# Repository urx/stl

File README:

STL - Sequential Tail Lights
============================

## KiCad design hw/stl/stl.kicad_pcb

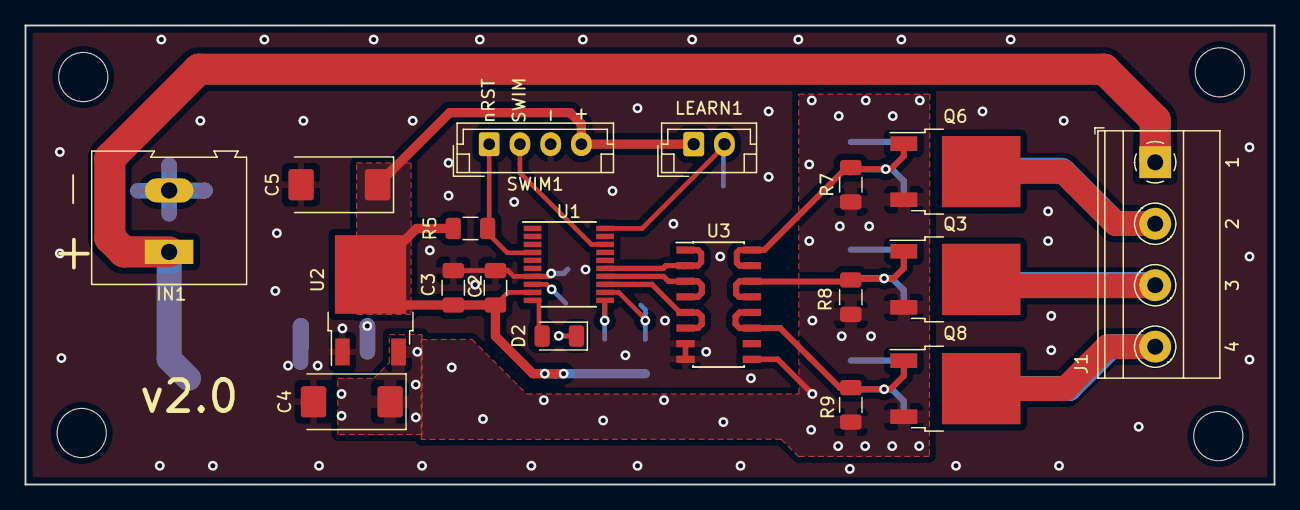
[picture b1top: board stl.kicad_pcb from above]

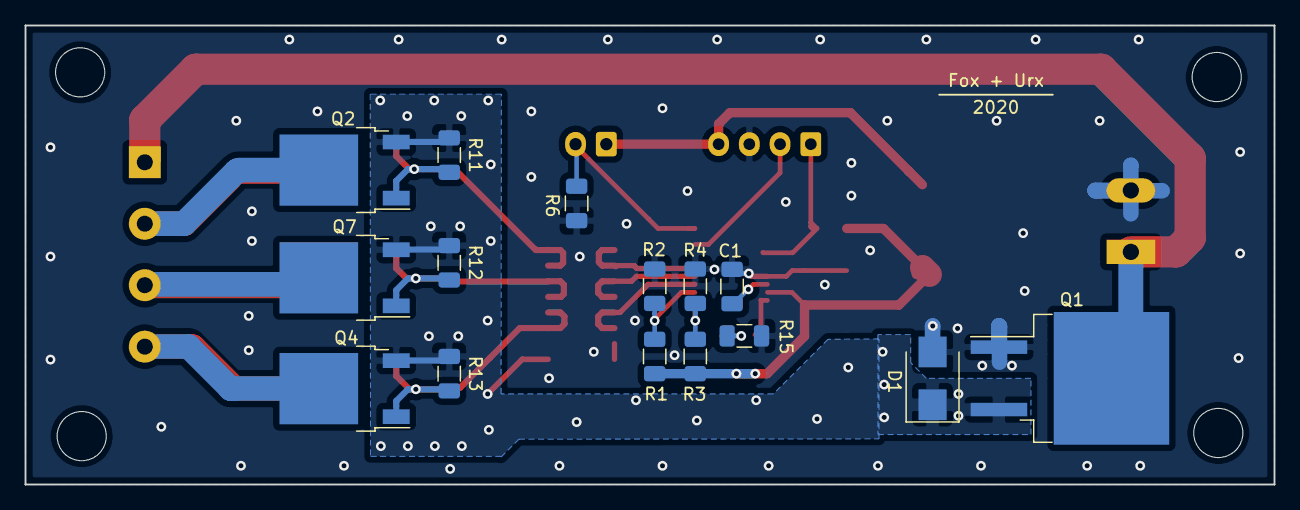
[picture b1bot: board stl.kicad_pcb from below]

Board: 2 copper layers, 101.6 x 37.3 mm, 34 parts (15 on the bottom side), 21 nets.

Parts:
C1, C3: 1uF; C_1206_3216Metric
C2: 0.1uF; C_1206_3216Metric
C4: 1uF; CP_EIA-7343-15_Kemet-W
C5: 10uF; CP_EIA-7343-15_Kemet-W
D1: SMBJ15A; D_SMB
D2: LED; LED_1206_3216Metric
IN1: Screw_Terminal_01x02; TerminalBlock_Altech_AK300-2_P5.00mm
J1: Screw_Terminal_01x04; TerminalBlock_Phoenix_MKDS-1,5-4_1x04_P5.00mm_Horizontal
LEARN1: Conn_01x02_Male; JST_EH_B02B-EH-A_1x02_P2.50mm_Vertical
Q1: IRF4905; TO-263-2
Q2: IRFR5505TRLPBF; TO-252-2
Q3, Q4, Q6, Q7, Q8: 5505; TO-252-2
R1, R2, R3, R4, R5, R6, R7, R8, R9, R11, R12, R13: 1K; R_1206_3216Metric
R15: 68; R_1206_3216Metric
SWIM1: Conn_01x04_Male; JST_EH_B04B-EH-A_1x04_P2.50mm_Vertical
U1: STM8S003F3P; TSSOP-20_4.4x6.5mm_P0.65mm
U2: LM1117-3.3; TO-252-2
U3: ULN2003A; SOIC-16_3.9x9.9mm_P1.27mm

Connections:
+3V3: C2.2, C3.2, C5.1, LEARN1.1, R1.2, R3.2, R5.2, SWIM1.4, U1.9, U2.2
+12V: C4.1, D1.1, Q1.3, Q2.3, Q3.3, Q4.3, Q6.3, Q7.3, Q8.3, R7.2, R8.2, R9.2, R11.2, R12.2, R13.2, U2.3, U3.9
+BATT: IN1.1, J1.1, Q1.2
CNT1: R1.1, R2.2, U1.12
CNT2: R3.1, R4.2, U1.11
GND: C1.1, C2.1, C3.1, C4.2, C5.2, D1.2, IN1.2, Q1.1, R2.1, R4.1, R6.1, R15.2, SWIM1.3, U1.7, U2.1, U3.7, U3.8
L2_STM_OUT: U1.13, U3.5, U3.6
L3_STM_OUT: U1.14, U3.3, U3.4
L4_STM_OUT: U1.15, U3.1, U3.2
LEARN: LEARN1.2, R6.2, U1.20
NRST: R5.1, SWIM1.1, U1.4
unnamed: C1.2, U1.8
unnamed: D2.1, R15.1
unnamed: D2.2, U1.10
SWIM: SWIM1.2, U1.18
lamp2_ctrl: Q2.1, Q6.1, R7.1, R11.1, U3.15, U3.16
lamp2_out: J1.2, Q2.2, Q6.2
lamp3_ctrl: Q3.1, Q7.1, R8.1, R12.1, U3.13, U3.14
lamp3_out: J1.3, Q3.2, Q7.2
lamp4_ctrl: Q4.1, Q8.1, R9.1, R13.1, U3.11, U3.12
lamp4_out: J1.4, Q4.2, Q8.2

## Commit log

2017-04-10 adds .gitignore file
2017-04-10 Adds basicaly 555 timer schematic for 300ms period
    TODO:
    * develop CD4017 counter schematic with jumper based scaling
    * develop 5V power supply
    * develop revers voltage protection
    * develop fuse
    * develop antistatic protection
2017-04-11 Adds basicaly 555 timer schematic for 300ms period TODO: * develop 5V power supply * develop revers voltage protection * develop fuse * develop antistatic protection * develop MOSFET-base load control
2017-04-11 Adds power mosfets, removes unnecessary 7805 TODO: * develop revers voltage protection * develop fuse * develop antistatic protection
2017-04-12 WIP: input voltage spike and reverse protection
    Also adds wago 508 screw connectors
    TODO:
    * develop fuse
    * develop antistatic protection
2017-04-13 mainboard in progress
2017-04-14 board and schematics done
2017-04-17 improve routing power polygones
2017-07-28 No more 555 and 4017. STM8 instead.
2017-08-02 Added 'LEARN' jumper
2017-09-19 all schematics related stuff moved into hw directory
2017-09-19 Initial commit of firmware. led blinker now
2017-09-19 improve readme :)
2018-02-09 switched to stm8spl.lib
2018-02-12 .gitignore added
2018-02-12 build on Darwin host
2018-02-12 removed trash code
2018-02-12 partially working, need to be tested
2018-02-12 it blinks. TODO: * fist TIM2 interrupts fires up immediatelly * implement learn procedure
2018-05-07 temporary disable learning by ifdef
2019-05-21 MISC: adds stm8spl as submodule
2019-05-21 update stm8spl head
2019-05-24 wip: build system
2019-05-28 sublime stuff
2019-05-28 MISC: clean *.adb files
2019-10-18 proper submodule for stm8spl
2019-12-07 MISC: schematic in kicad
2019-12-08 WIP: tracing in progress
2019-12-12 WIP: draft tracing
2020-01-08 cosmetic changes
2020-01-10 [FEAT]: pcb is traced, v2.0
2020-01-10 [FEAT]: resistors R1-R4 moved together
2020-01-10 [FEAT]: edited missed via
2020-01-15 Some writings, adds gerbers
